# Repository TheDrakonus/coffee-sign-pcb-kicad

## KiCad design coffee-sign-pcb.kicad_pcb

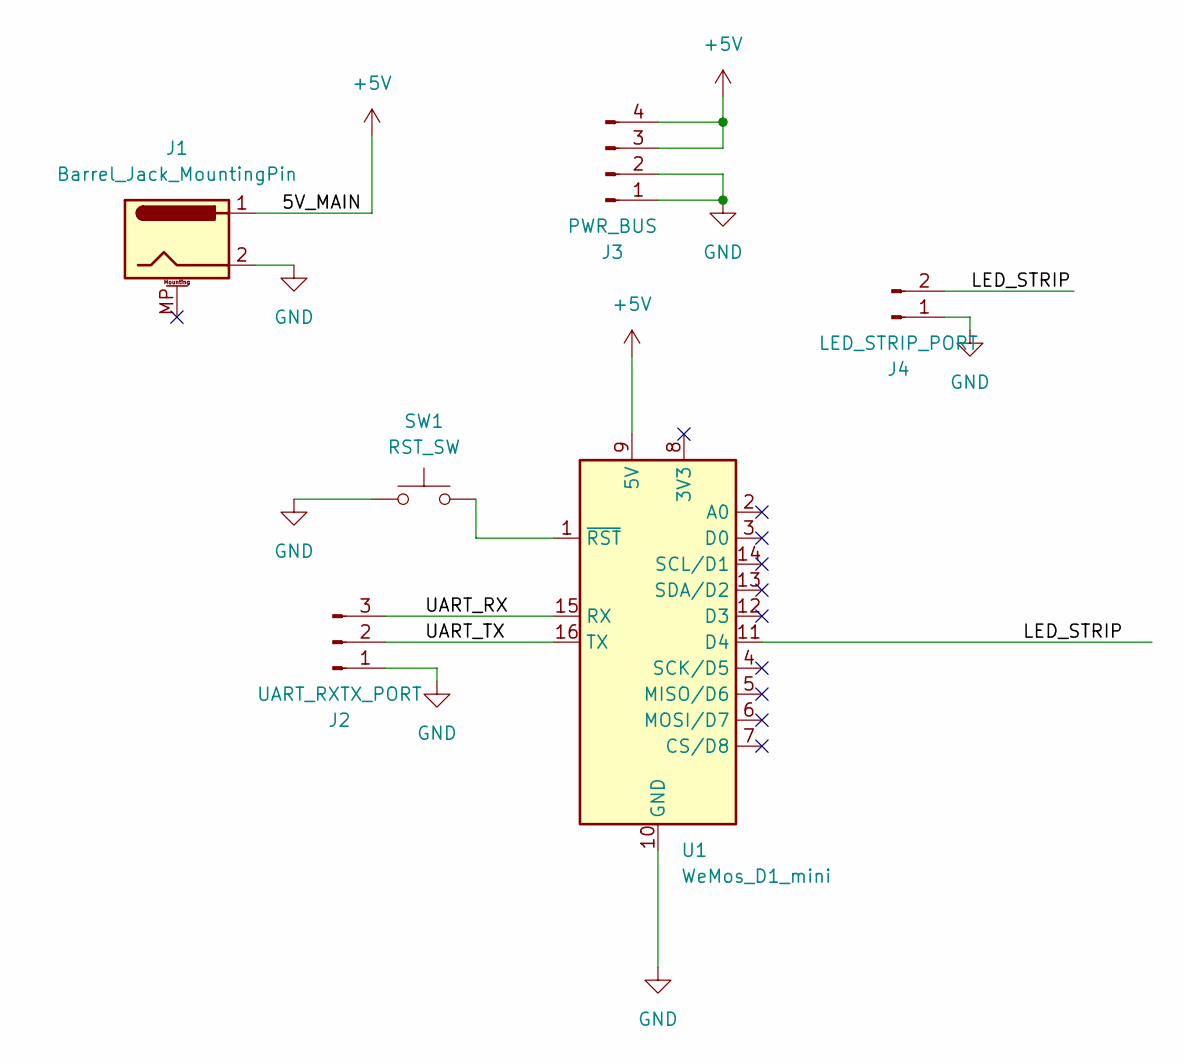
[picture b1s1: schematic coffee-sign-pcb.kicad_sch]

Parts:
J1: Barrel_Jack_MountingPin; BarrelJack_CUI_PJ-063AH_Horizontal
J2: UART_RXTX_PORT; PinHeader_1x03_P2.54mm_Vertical
J3: PWR_BUS; JST_XH_B4B-XH-A_1x04_P2.50mm_Vertical
J4: LED_STRIP_PORT; JST_XH_B2B-XH-A_1x02_P2.50mm_Vertical
SW1: RST_SW; SW_SPST_SKQG_WithStem
U1: WeMos_D1_mini; WEMOS_D1_mini_light

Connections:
+5V: J1.1, J3.3, J3.4, U1.9 (5V)
/LED_STRIP: J4.2, U1.11 (D4)
/UART_RX: J2.3, U1.15 (RX)
/UART_TX: J2.2, U1.16 (TX)
GND: J1.2, J2.1, J3.1, J3.2, J4.1, SW1.1, U1.10 (GND)
unnamed: SW1.2, U1.1 (~RST)

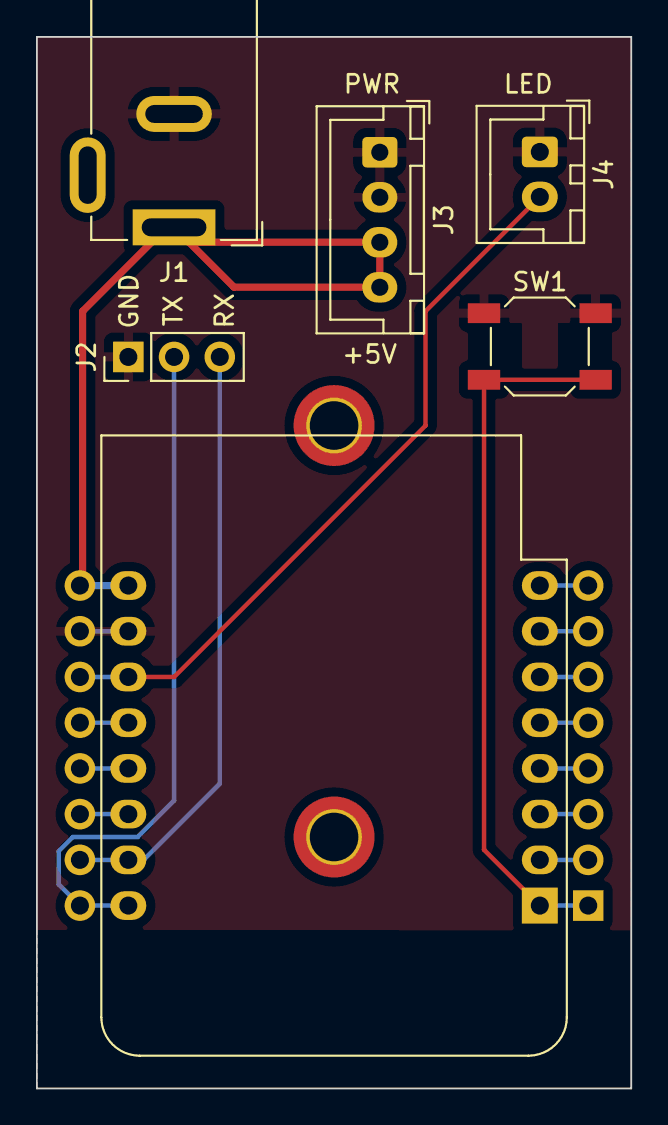
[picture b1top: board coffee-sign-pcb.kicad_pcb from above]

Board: 2 copper layers, 33.0 x 58.4 mm, 6 parts (0 on the bottom side), 6 nets.
